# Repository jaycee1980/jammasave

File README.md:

# jammasave
A CRT power saver for JAMMA arcade cabinets.

At the [Centre for Computing History](http://www.computinghistory.org.uk) we have a few arcade cabinets for visitors to play on. These traditionally use CRT monitors -  CRT's are a problem, because they wear out with use, and draw quite a bit of power. The machines stand idle often, so the CRT displays are needlessly on, being worn down and costing extra money to run. As CRT's are no longer being made, it can be problematic to replace them when they fail.

PC's solved this issue by having screensavers that power off the monitor when the machine is idle. However, arcade machines typically run an "attract" mode to entice people to play on them, thus there is no such setting.

So what do we do ? Solve it with extra hardware of course :)

## How it works

The board is designed to be wired to 5V power (easily obtainable in an arcade cabinet), and has a relay which is normally switched on, but switches off when a timeout period expires. There are  16 "wire-OR'd" inputs which are connected to the JAMMA connectors input pins (See https://wiki.arcadeotaku.com/w/JAMMA for more info). When any of these 16 inputs are pulled low (i.e. the user presses a button or pushes a direction), the timer is reset. The CRT's power feed can be wired through this relay so that it is switched off when the timer expires.

A preset potentiometer allows the timeout period to be adjusted from 30 minutes to 1½ hours. This can be further adjusted in the software if required.
A jumper can also put the board into "disable" mode, where the relay is switched on and nothing else happens. This is useful for servicing.

# Details

The design is based around an [Atmel ATtiny13 microcontroller](https://www.microchip.com/wwwproducts/en/ATtiny13). An internal 4.8MHz oscillator means there is no need for an external timing crystal.

The internal ADC allows a simple preset potentiometer, wired as a potential divider, to be used in order to set the timeout delay. The ADC simply reads a value between 0-1023 which is then used to set the initial value of the timeout counter.

One GPIO port is configured as an output, and used to control a a "sugar cube" type relay, via a BC337 transistor. The relay is a 5V type so that only a 5V supply is required. This relay then controls the CRT by switching it's power feed.

JAMMA inputs are active low, so this means that multiple inputs can be catered for simply by using diodes. A GPIO pin is configured as an input, which is normally pulled up th +5V via a 100K resistor. A path to ground through any one of the diodes pulls the input low, which is detected by using pin change interrupts.

The timeout period is implemented using Timer/Counter 0. This is configured to generate ~500 ticks/second. This is used to decrement a tiemout counter which is initially set according to the timeout period required. Once this counter reaches zero, the relay is switched off. If the pin change interrupt fires due to an input, the timeout counter is reset.

# Whats in this repo

This repo contains the EAGLE design files, Gerber files suitable for manufacturing, the C source code and Atmel Studio project files used to compile the code.

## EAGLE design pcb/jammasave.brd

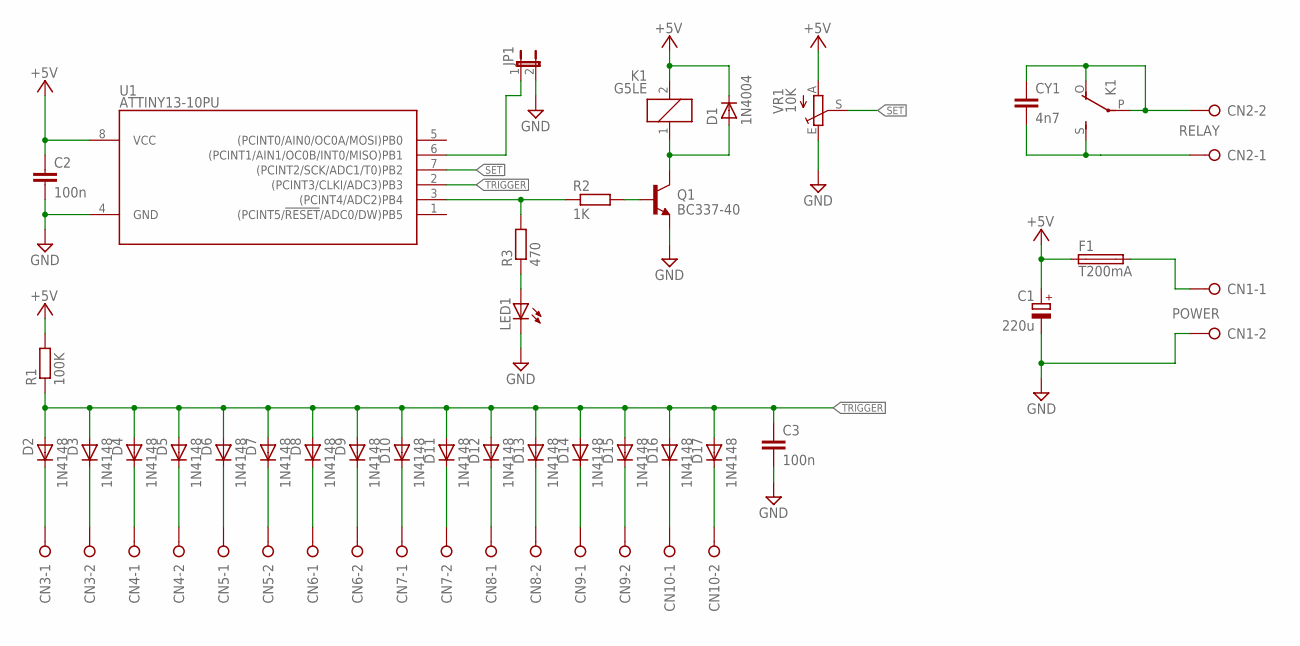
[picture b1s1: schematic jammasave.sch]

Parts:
C1: 220u; E3,5-8
C2, C3: 100n; C050-035X075
CN1: POWER; W237-132
CN2: RELAY; W237-2N
CN3, CN4, CN5, CN6, CN7, CN8, CN9, CN10: W237-02P; W237-132
CY1: 4n7; YC10B5
D1: 1N4004; DO41-10
D2, D3, D4, D5, D6, D7, D8, D9, D10, D11, D12, D13, D14, D15, D16, D17: 1N4148; DO35-7
F1: T200mA; TE5
JP1: JP1E; JP1
K1: G5LE
LED1: LED3MM
Q1: BC337-40; TO92-254
R1: 100K; 0207/10
R2: 1K; 0207/10
R3: 470; 0207/10
U1: ATTINY13-10PU; DIL08
VR1: 10K; CA6V

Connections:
+5V: C1.+, C2.1, D1.K (C), F1.1, K1.2, R1.2, U1.8 (VCC), VR1.A
GND: C1.-, C2.2, C3.2, CN1.2, JP1.2, LED1.K (C), Q1.3 (E), U1.4 (GND), VR1.E
unnamed: Q1.2 (B), R2.2
unnamed: D1.A, K1.1, Q1.1 (C)
unnamed: R2.1, R3.2, U1.3 ((PCINT4/ADC2)PB4)
unnamed: CN1.1, F1.2
unnamed: LED1.A, R3.1
unnamed: JP1.1, U1.6 ((PCINT1/AIN1/OC0B/INT0/MISO)PB1)
unnamed: CN2.2, CY1.1, K1.O, K1.P
unnamed: CN2.1, CY1.2, K1.S
unnamed: CN3.1, D2.K (C)
unnamed: CN3.2, D3.K (C)
unnamed: CN4.1, D4.K (C)
unnamed: CN4.2, D5.K (C)
unnamed: CN5.1, D6.K (C)
unnamed: CN5.2, D7.K (C)
unnamed: CN6.1, D8.K (C)
unnamed: CN6.2, D9.K (C)
unnamed: CN7.1, D10.K (C)
unnamed: CN7.2, D11.K (C)
unnamed: CN8.1, D12.K (C)
unnamed: CN8.2, D13.K (C)
unnamed: CN9.1, D14.K (C)
unnamed: CN9.2, D15.K (C)
unnamed: CN10.1, D16.K (C)
unnamed: CN10.2, D17.K (C)
SET: U1.7 ((PCINT2/SCK/ADC1/T0)PB2), VR1.S
TRIGGER: C3.1, D2.A, D3.A, D4.A, D5.A, D6.A, D7.A, D8.A, D9.A, D10.A, D11.A, D12.A, D13.A, D14.A, D15.A, D16.A, D17.A, R1.1, U1.2 ((PCINT3/CLKI/ADC3)PB3)

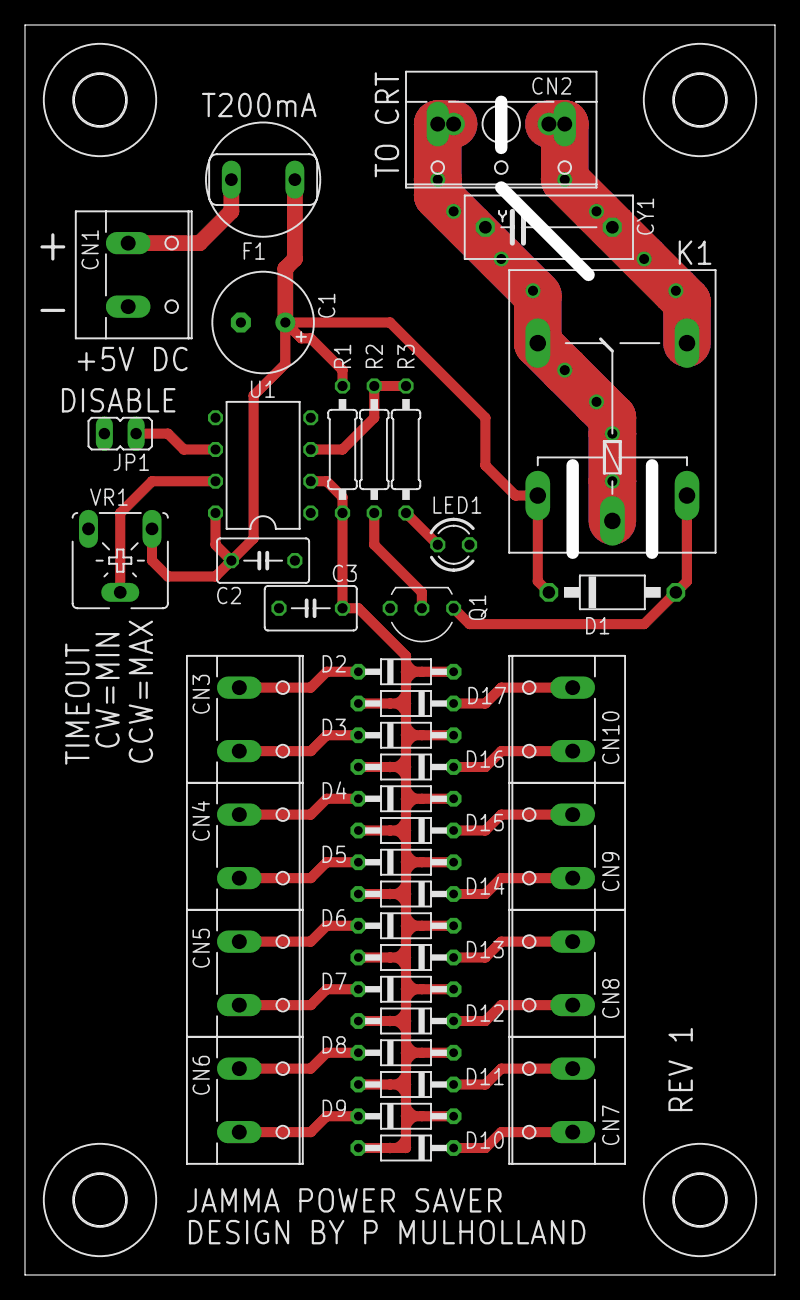
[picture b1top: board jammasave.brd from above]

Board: 2 copper layers, 59.0 x 99.0 mm, 45 parts (0 on the bottom side), 28 nets.

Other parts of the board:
U$1, U$2, U$3, U$4: 4,1

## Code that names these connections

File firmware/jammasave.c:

/*******************************************************************************************************************//**
	JAMMA cabinet power saver
	\author Peter Mulholland
***********************************************************************************************************************/

// avr-gcc -mmcu=attiny13a -Os -std=c99 jammasave.c -o jammasave.elf
// avrdude -p t13 -b 19200 -c usbasp-clone -P com4 -v -U flash:w:jammasave.elf -U hfuse:w:0xF8:m -U lfuse:w:0x71:m

#define F_CPU 4800000UL

#include <stdint.h>
#include <avr/io.h>
#include <avr/sleep.h>
#include <avr/wdt.h>
#include <avr/interrupt.h>
#include <avr/cpufunc.h>
#include <avr/pgmspace.h>

//----------------------------------------------------------------------------------------------------------------------
// Fuse settings

FUSES = {
	.low = (FUSE_SPIEN & FUSE_SUT1 & FUSE_SUT0 & FUSE_CKSEL1),		// SPI programming, 4.8MHz internal clock, minimal reset delay
	.high = (FUSE_BODLEVEL1 & FUSE_BODLEVEL0 & FUSE_RSTDISBL)		// brownout at 4.3v, reset pin disabled
};

//----------------------------------------------------------------------------------------------------------------------
// Constants and Defines

// The timer ticks at 75KHz. A count of 150 means our ISR triggers every 5KHz
#define TIMER_COUNT		(256-150)

// So, 500 ticks = 1 second.
// In reality it's a little inaccurate because the 4.8MHz internal clock isn't that accurate.
#define TIMER_TICKS_PER_SEC		500

//----------------------------------------------------------------------------------------------------------------------
// PROGMEM data

static const char c_credits[] __attribute__((used)) PROGMEM = "JAMMA Power Saver built " __DATE__ " " __TIME__;

//----------------------------------------------------------------------------------------------------------------------
// EEMEM data

//----------------------------------------------------------------------------------------------------------------------
// Global variables

uint32_t g_timer = 0;
uint32_t g_timeout = 0;

//----------------------------------------------------------------------------------------------------------------------
// Local Functions

uint16_t read_adc()
{
	ADCSRA |= (1 << ADSC);									// Start conversion
	while (!(ADCSRA & (1 << ADIF)));						// Wait for it to complete
	ADCSRA |= (1 << ADIF);									// Clear completion bit

	return ADCW;
}

void read_timeout_setting()
{
	// Set up ADC with ADC1 (PB2) as the input
	DIDR0 = (1 << ADC1D);									// Disable digital IO on PB2
	ADMUX = (1 << MUX1);									// Use Vcc as reference, right adjusted result, input from ADC1 (PB2)
	ADCSRB = 0;
	ADCSRA = (1 << ADEN) | (1 << ADPS2) | (1 << ADPS0);		// Enable ADC, no interrupt, CLK/32 (150KHz)
	_NOP();
	_NOP();

	// Do some dummy readings to allow ADC to settle
	for (uint8_t i = 0; i < 8; i++)
		read_adc();

	// Read ADC for timeout scale value (0 - 511)
	uint16_t tcnt = read_adc() >> 1;

	// Set timer to the timeout count - between 1/2 hour and 1 1/2 hour.
	//	g_timeout =  1800 + ((((3600 * 32) / 512) * (uint32_t) tcnt) / 32);
	g_timeout  = ((225UL * (uint32_t) tcnt) / 32UL ) +	300UL; //+ 1800UL;
	g_timeout *= (uint32_t) TIMER_TICKS_PER_SEC;

	// We don't use the ADC any more, so turn it off
	ADCSRA = 0;
	PRR = (1 << PRADC);
}

//----------------------------------------------------------------------------------------------------------------------
// ISR's

ISR(TIM0_OVF_vect)
{
	// If we go over the timeout count, turn the relay off and stop the timer
	// We then wait for a pin change interrupt to wake things up again

	if (g_timer-- == 0)
	{
		// Turn relay off
		PORTB &= ~(1 << PORTB4);

		// Stop the timer
		TCCR0B = 0;
	}
	else
	{
		// Go for another round
		TCNT0 = TIMER_COUNT;
	}

	TIFR0 &= ~(1 << TOV0);
}

ISR(PCINT0_vect)
{
	// If our pin change was low, the user pressed a control. Stop timer, and turn the relay on if it isn't.
	// if our pin change was high, reset and start the timer again.
	// This behaviour means that a stuck-on input will only result in the timeout never happening...
	if ((PINB & (1 << PINB3)) == 0)
	{
		// Turn the relay on if it isn't already
		PORTB |= (1 << PORTB4);

		// Stop the timer
		TCCR0B = 0;
	}
	else
	{
		// Reset and start the timer
		g_timer = g_timeout;

		TCNT0 = TIMER_COUNT;
		TCCR0B = (1 << CS01) | (1 << CS00);
	}
}

//----------------------------------------------------------------------------------------------------------------------
// Main

void main(void) __attribute__((noreturn));

void main(void)
{
	// Disable the watchdog timer
	wdt_disable();

	// Enable pullup on PB1, set output ports low
	PORTB = (1 << PORTB1);

	// Set PB4 as output (relay control), the rest to inputs
	DDRB = (1 << DDB4);

	// Wait for port state to synchronise before reading it
	_NOP();
	_NOP();

	// Check if the "disable" jumper connected to PB1 is present (PB1 will be pulled low)
	// If it is, we don't do anything else - just turn on the relay and go to sleep permanently

	if (!(PINB & (1 << PINB1)))
	{
		// Turn relay on
		PORTB |= (1 << PORTB4);

		// We never wake up again...
		set_sleep_mode(SLEEP_MODE_PWR_DOWN);
	}
	else
	{
		// Set up pin change interrupt for PB3
		PCMSK = (1 << PCINT3);
		GIMSK = (1 << PCIE);

		// Read the ADC for our timeout setting
		read_timeout_setting();
		//g_timeout = 1800;

		// Turn relay on
		PORTB |= (1 << PORTB4);

		// Set timeout counter
		g_timer = g_timeout;

		// Set up the overflow timer. 4.8MHz / 64 = ticks at 75KHz.
		TIMSK0 = (1 << TOIE0);					// TIMER0_OVF interrupt on
		TIFR0 = 0;								// Clear timer flags
		TCCR0A = 0;								// No compare match output, normal waveform mode

		TCNT0 = TIMER_COUNT;
		TCCR0B = (1 << CS01) | (1 << CS00);		// Set divider and start

		sei();									// Enable interrupts so that timer overflow and pin change wake us up

		// Set our sleep mode so timer and pin change interrupts work
		set_sleep_mode(SLEEP_MODE_IDLE);
	}

	// Interrupts do the rest, sit here and sleep
	for (;;)
	{
		sleep_enable();
		sleep_cpu();
	}
}

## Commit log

2021-05-25 Initial checkin
2021-05-25 PDF of the schematic and a photo of the assembled board
2021-05-25 Updated Atmel Studio project settings
2021-05-25 Optimised and commented code
2021-05-25 Prebuilt firmware in HEX format for programming
2021-05-25 Make sure TOV0 bit is always cleared after a timer overflow interrupt
2021-05-25 Bill of materials
2021-05-25 Corrected BOM value for C1
2021-05-26 Correct potential underflow issue on timeout counter
2021-05-26 Make the timeout period start at 5 minutes (mostly for testing but who knows)
2022-12-05 Remove CCH "branding"
